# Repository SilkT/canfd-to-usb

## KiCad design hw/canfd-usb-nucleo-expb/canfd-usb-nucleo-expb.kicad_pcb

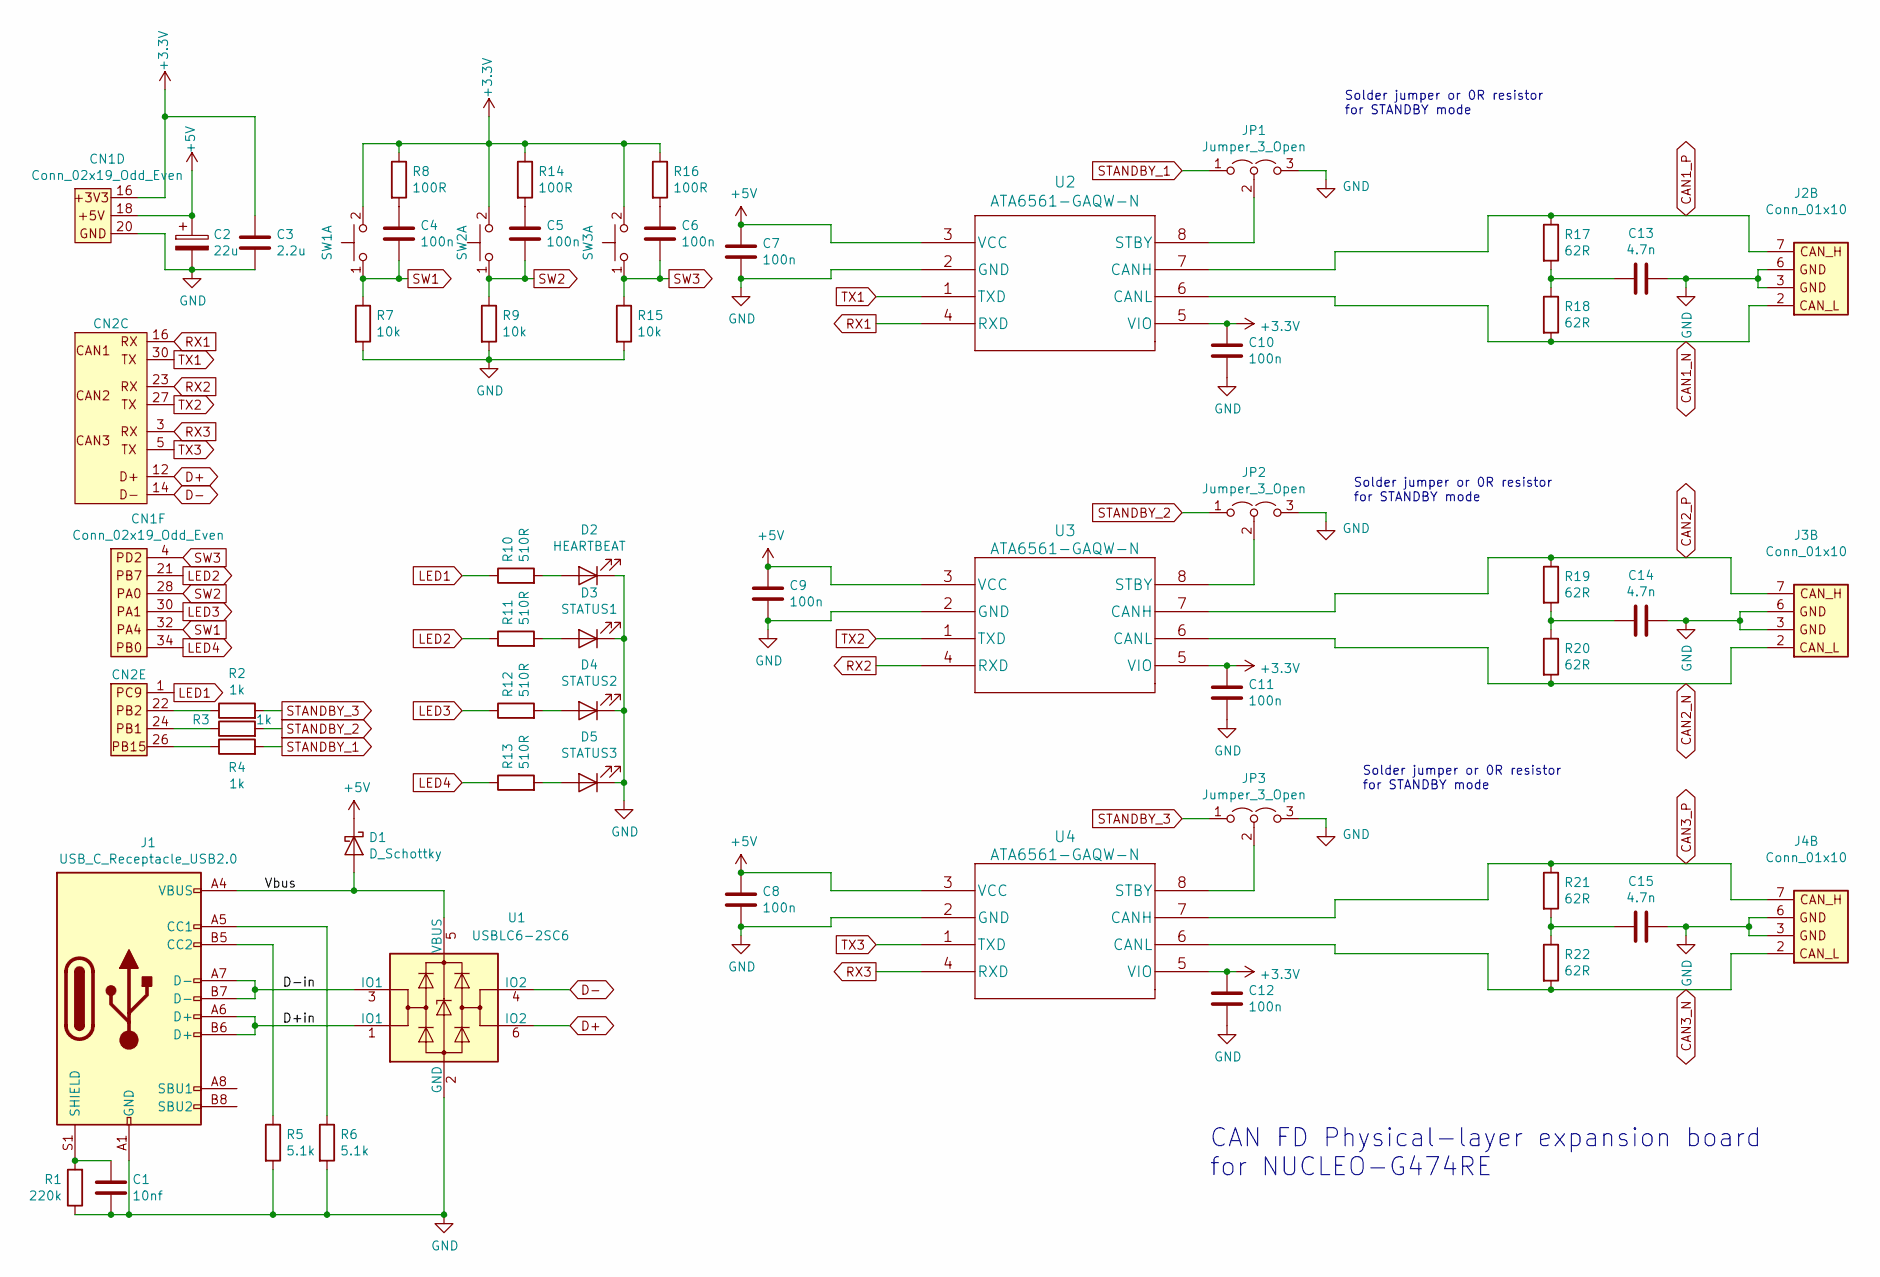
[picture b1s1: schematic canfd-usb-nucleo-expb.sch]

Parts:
C1: 10nf; C_0805_HandSoldering
C2: 22u; C_1206_3216Metric
C3: 2.2u; C_0805_HandSoldering
C4, C5, C6, C7, C8, C9, C10, C11, C12: 100n; C_0805_HandSoldering
C13, C14, C15: 4.7n; C_0805_HandSoldering
CN1: Conn_02x19_Odd_Even; Pin_Header_Straight_2x19_Pitch2.54mm
CN2: CONN; Pin_Header_Straight_2x19_Pitch2.54mm
D1: D_Schottky; D_SOD-123
D2: HEARTBEAT; LED_D3.0mm
D3: STATUS1; LED_D3.0mm
D4: STATUS2; LED_D3.0mm
D5: STATUS3; LED_D3.0mm
J1: USB_C_Receptacle_USB2.0; L-KLS1-TIPEC-B
J2, J3, J4: Conn_01x10; IDC-Header_2x05_P2.54mm_Vertical
JP1, JP2, JP3: Jumper_3_Open; SolderJumper-3_P1.3mm_Open_RoundedPad1.0x1.5mm
R1: 220k; R_0805_HandSoldering
R2, R3, R4: 1k; R_0805_HandSoldering
R5, R6: 5.1k; R_0805_HandSoldering
R7, R9, R15: 10k; R_0805_HandSoldering
R8, R14, R16: 100R; R_0805_HandSoldering
R10, R11, R12, R13: 510R; R_0805_HandSoldering
R17, R18, R19, R20, R21, R22: 62R; R_0805_HandSoldering
SW1, SW2, SW3: SW_Push_Dual_x2; SW_PUSH_6mm
U1: USBLC6-2SC6; SOT-23-6_Handsoldering
U2, U3, U4: ATA6561-GAQW-N; SOIC-8_3.9x4.9mm_Pitch1.27mm

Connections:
+3V3: C3.1, C10.1, C11.1, C12.1, CN1.16, R8.1, R14.1, R16.1, SW1.2 (D), SW2.2 (D), SW3.2 (D), U2.5 (VIO), U3.5 (VIO), U4.5 (VIO)
+5V: C2.1, C7.1, C8.1, C9.1, CN1.18, D1.1 (K), U2.3 (VCC), U3.3 (VCC), U4.3 (VCC)
/D+in: J1.A6 (D+), J1.B6 (D+), U1.1 (IO1)
/D-in: J1.A7 (D-), J1.B7 (D-), U1.3 (IO1)
/Vbus: D1.2 (A), J1.A4 (VBUS), J1.A9 (VBUS), J1.B4 (VBUS), J1.B9 (VBUS), U1.5 (VBUS)
CAN1_N: J2.2, R18.2, U2.6 (CANL)
CAN1_P: J2.7, R17.1, U2.7 (CANH)
CAN2_N: J3.2, R20.2, U3.6 (CANL)
CAN2_P: J3.7, R19.1, U3.7 (CANH)
CAN3_N: J4.2, R22.2, U4.6 (CANL)
CAN3_P: J4.7, R21.1, U4.7 (CANH)
D+: CN2.12, U1.6 (IO2)
D-: CN2.14, U1.4 (IO2)
GND: C1.2, C2.2, C3.2, C7.2, C8.2, C9.2, C10.2, C11.2, C12.2, C13.2, C14.2, C15.2, CN1.20, D2.1 (K), D3.1 (K), D4.1 (K), D5.1 (K), J1.A1 (GND), J1.A12 (GND), J1.B1 (GND), J1.B12 (GND), J2.3, J2.6, J3.3, J3.6, J4.3, J4.6, JP1.3 (B), JP2.3 (B), JP3.3 (B), R1.1, R5.2, R6.2, R7.2, R9.2, R15.2, U1.2 (GND), U2.2 (GND), U3.2 (GND), U4.2 (GND)
LED1: CN2.1, R10.1
LED2: CN1.21, R11.1
LED3: CN1.30, R12.1
LED4: CN1.34, R13.1
unnamed: C1.1, J1.S1 (SHIELD), R1.2
unnamed: C4.1, R8.2
unnamed: C5.1, R14.2
unnamed: C6.1, R16.2
unnamed: C13.1, R17.2, R18.1
unnamed: C14.1, R19.2, R20.1
unnamed: C15.1, R21.2, R22.1
unnamed: CN2.22, R2.1
unnamed: CN2.24, R3.1
unnamed: CN2.26, R4.1
unnamed: D2.2 (A), R10.2
unnamed: D3.2 (A), R11.2
unnamed: D4.2 (A), R12.2
unnamed: D5.2 (A), R13.2
unnamed: J1.A5 (CC1), R6.1
unnamed: J1.B5 (CC2), R5.1
unnamed: JP1.2 (C), U2.8 (STBY)
unnamed: JP2.2 (C), U3.8 (STBY)
unnamed: JP3.2 (C), U4.8 (STBY)
RX1: CN2.16, U2.4 (RXD)
RX2: CN2.23, U3.4 (RXD)
RX3: CN2.3, U4.4 (RXD)
STANDBY_1: JP1.1 (A), R4.2
STANDBY_2: JP2.1 (A), R3.2
STANDBY_3: JP3.1 (A), R2.2
SW1: C4.2, CN1.32, R7.1, SW1.1 (C)
SW2: C5.2, CN1.28, R9.1, SW2.1 (C)
SW3: C6.2, CN1.4 (PD2), R15.1, SW3.1 (C)
TX1: CN2.30, U2.1 (TXD)
TX2: CN2.27, U3.1 (TXD)
TX3: CN2.5, U4.1 (TXD)

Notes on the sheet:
CAN FD Physical-layer expansion board for NUCLEO-G474RE
Solder jumper or 0R resistor for STANDBY mode

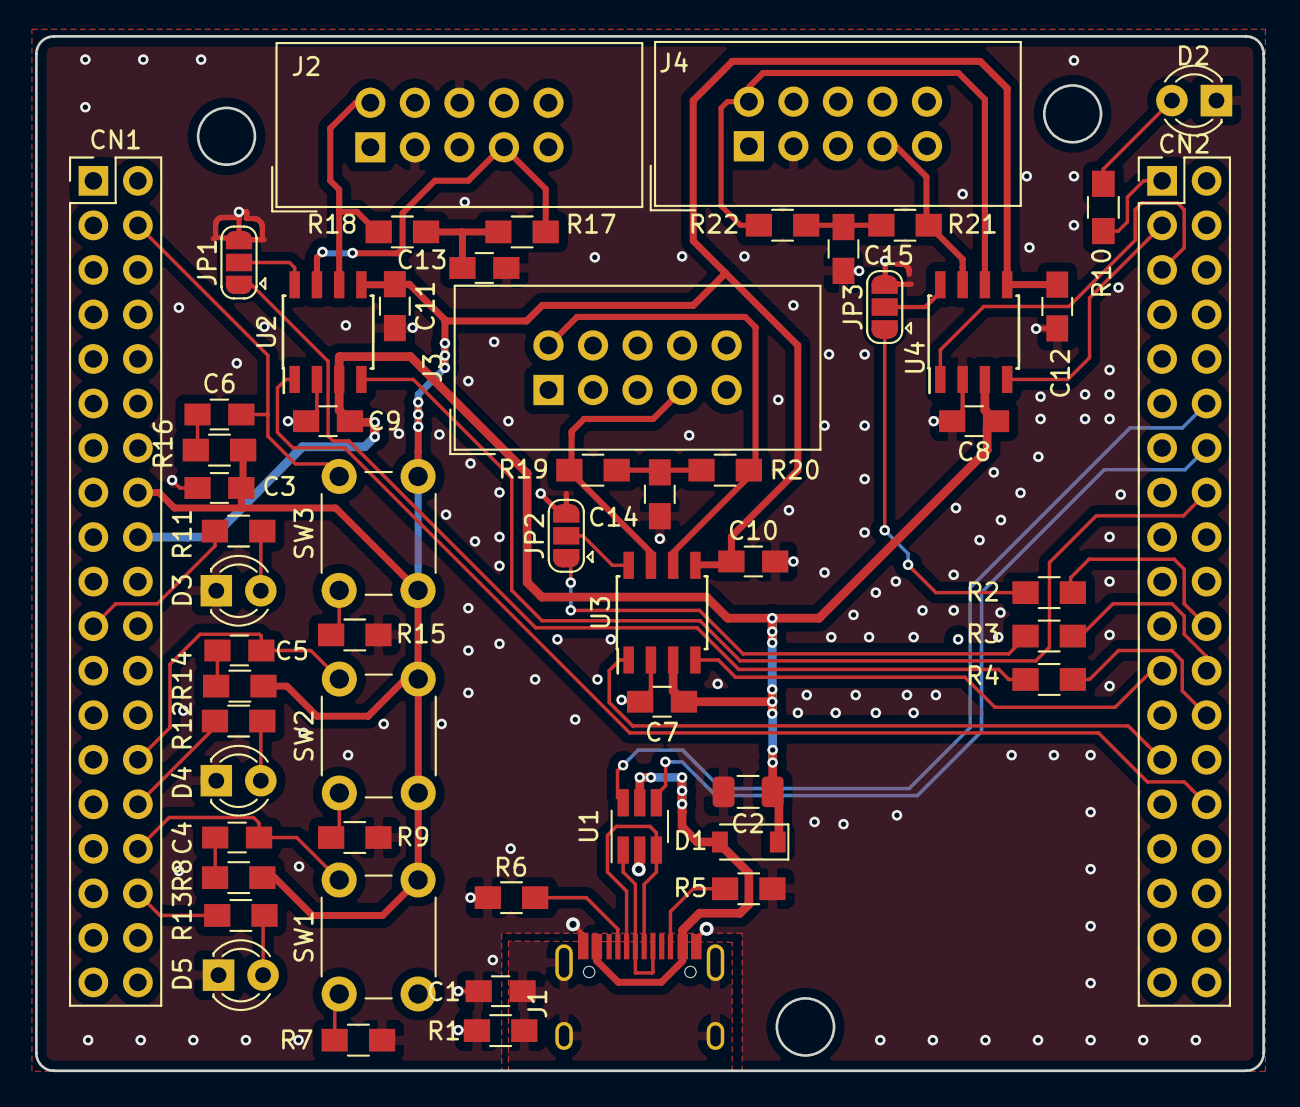
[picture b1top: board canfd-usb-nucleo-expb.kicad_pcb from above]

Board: 2 copper layers, 70.0 x 59.0 mm, 58 parts (0 on the bottom side), 49 nets.

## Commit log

2020-02-23 Folders structure
    Create folder structure.
    [hw] - folder for the hardware design
    [sw-mcu] - folder for the embedded software
    [sw-pc] - java command line application
2020-02-25 HW: Project created
    KiCAD project is created. Nucleo expansion board template is
    created in the project. ATA6561 transceiver is added to project library.
2020-02-28 HW: CAN transceiver with accompanying circuitry was added
    CAN transceiver, connectors from nucleo to shiled are added. USB type A for external flash memory also is added.
2020-03-02 HW: Schematic edit - buttons and LEDs
    Added buttons and LEDs to schematic, minor fixes in
    existing components. Assigned most components with
    their respective footprints.
2020-03-02 HW: Schematic update - BH connectors
    1. Added BH connectors for ribbon cable connection to CAN-bus.
    2. Hopefuly fixed the kicad library linking problem.
    Schematic is ready to be reviewed before
    laying out the PCB.
2020-03-03 HW: Schematic fixes, PCB outline fixes
    1. PCB outline is now a rectangle, arduino pins are removed
    2. 22u tantalum cap added on 5V rail
    3. USB termination resistors are removed as they are implemented
    in MCU's PHY
    4. Buttons are stronger pulled-up with 10k resistors instead of
    100k like on other stm boards, 100 Ohm resistors added in series
2020-03-10 HW: Added footprints for all components
    Created the footprint for USB-Type-C connector
    Added footprints for the rest of the components on the PCB.
    Started the mock-up placement of components on the board
2020-03-11 HW: Footprints and components layout
    Added footprints for all components and created a new one for USB
    connector. Started the components layout with positioning of all
    components on the PCB before laying out the traces.
2020-03-13 HW: PCB Layout: Part 1
    Fixed the USBLC6-2SC6 part;
    Routed most of the PHY can parts of the board.
2020-03-15 HW: PCB routing branched-off by AlexeyZ
    Seems like I've started some work in parallel with Stiwens
    so this is my version of the PCB routing from the last commit.
    Probably this branch will be deleted and not used in the final
    design but that's just a little bit of practice on my side.
2020-03-15 HW: First version of PCB layout
    First version of PCB layout is ready for review.
    Changed the assignments of pins for switches and status LEDs
    to ease the routing of traces.
    PCB's bottom layer is GND plane, most of the traces are placed
    on top layer. Ground planes are connected with via stitching on
    full area of the PCB.
2020-03-16 HW: PCB layout is ready to review
2020-03-18 HW: USB routes are fixed
2020-03-18 HW: PCB layout fix_1
    Power supply lines are re-routed
    More vias to Power supply lines are added
    USB ESD protection symbol on the schematic is changed
    ESD protection bridges beetwen data lines are removed
    LED positions are remaining unchanged
2020-03-18 HW: PCB small-fix
    Added thermal reliefs to Solder-Jumpers
    Slightly moved J2 and J4 to make clearence for mounting holes
    Moved R10 for the same reason
